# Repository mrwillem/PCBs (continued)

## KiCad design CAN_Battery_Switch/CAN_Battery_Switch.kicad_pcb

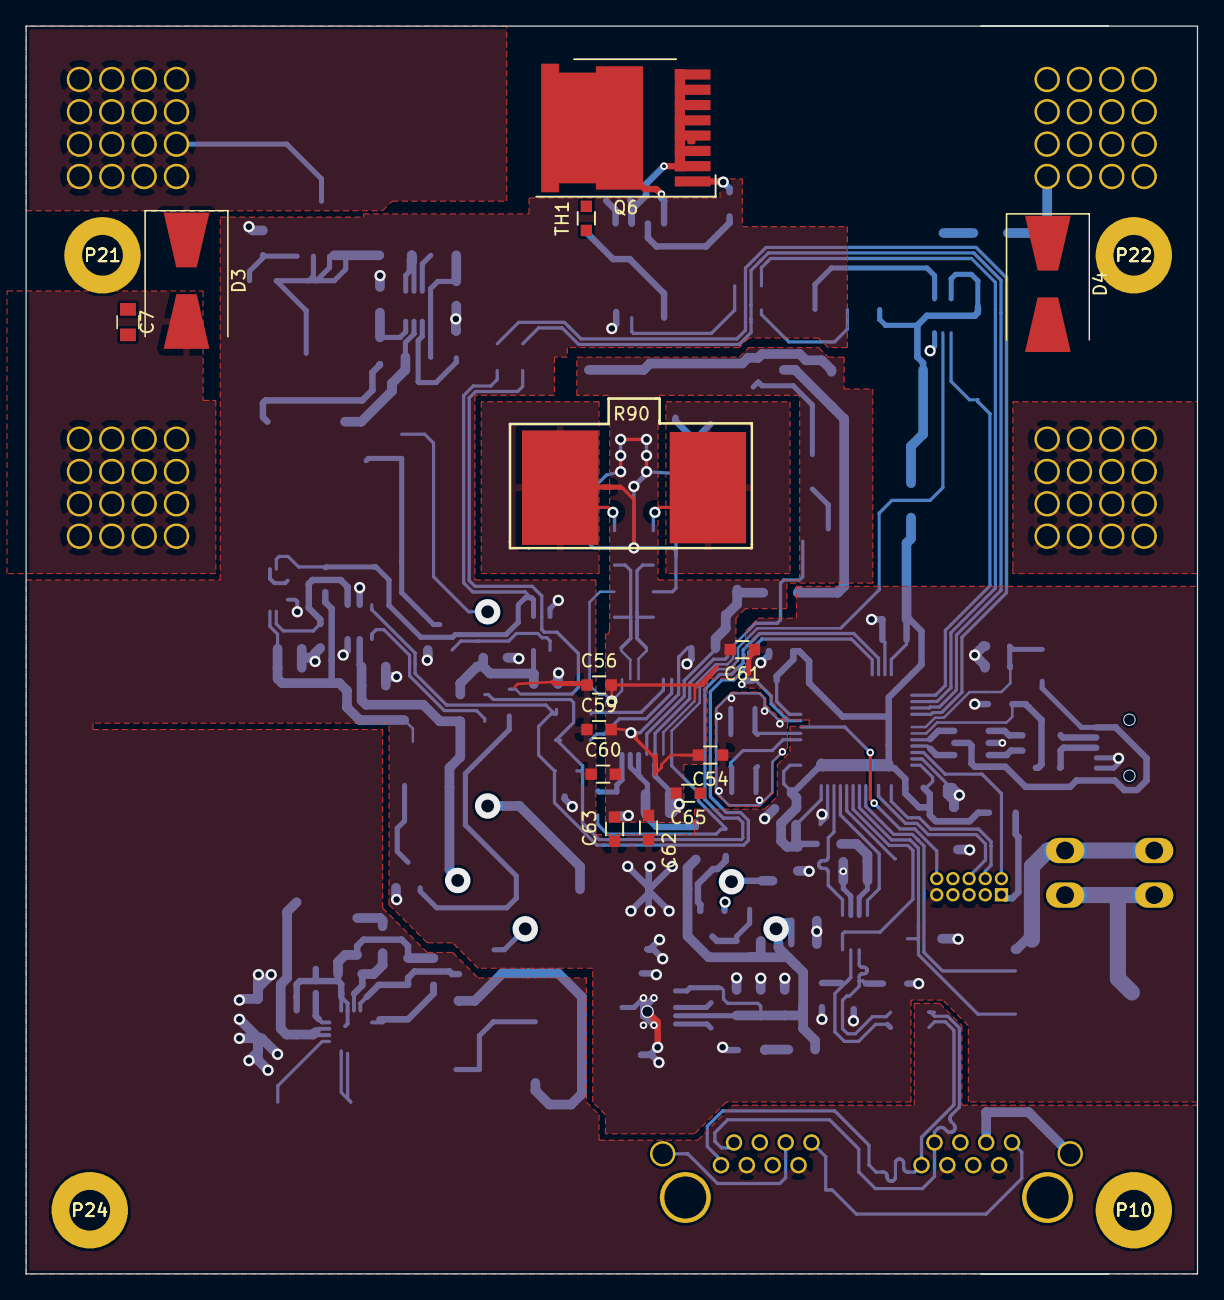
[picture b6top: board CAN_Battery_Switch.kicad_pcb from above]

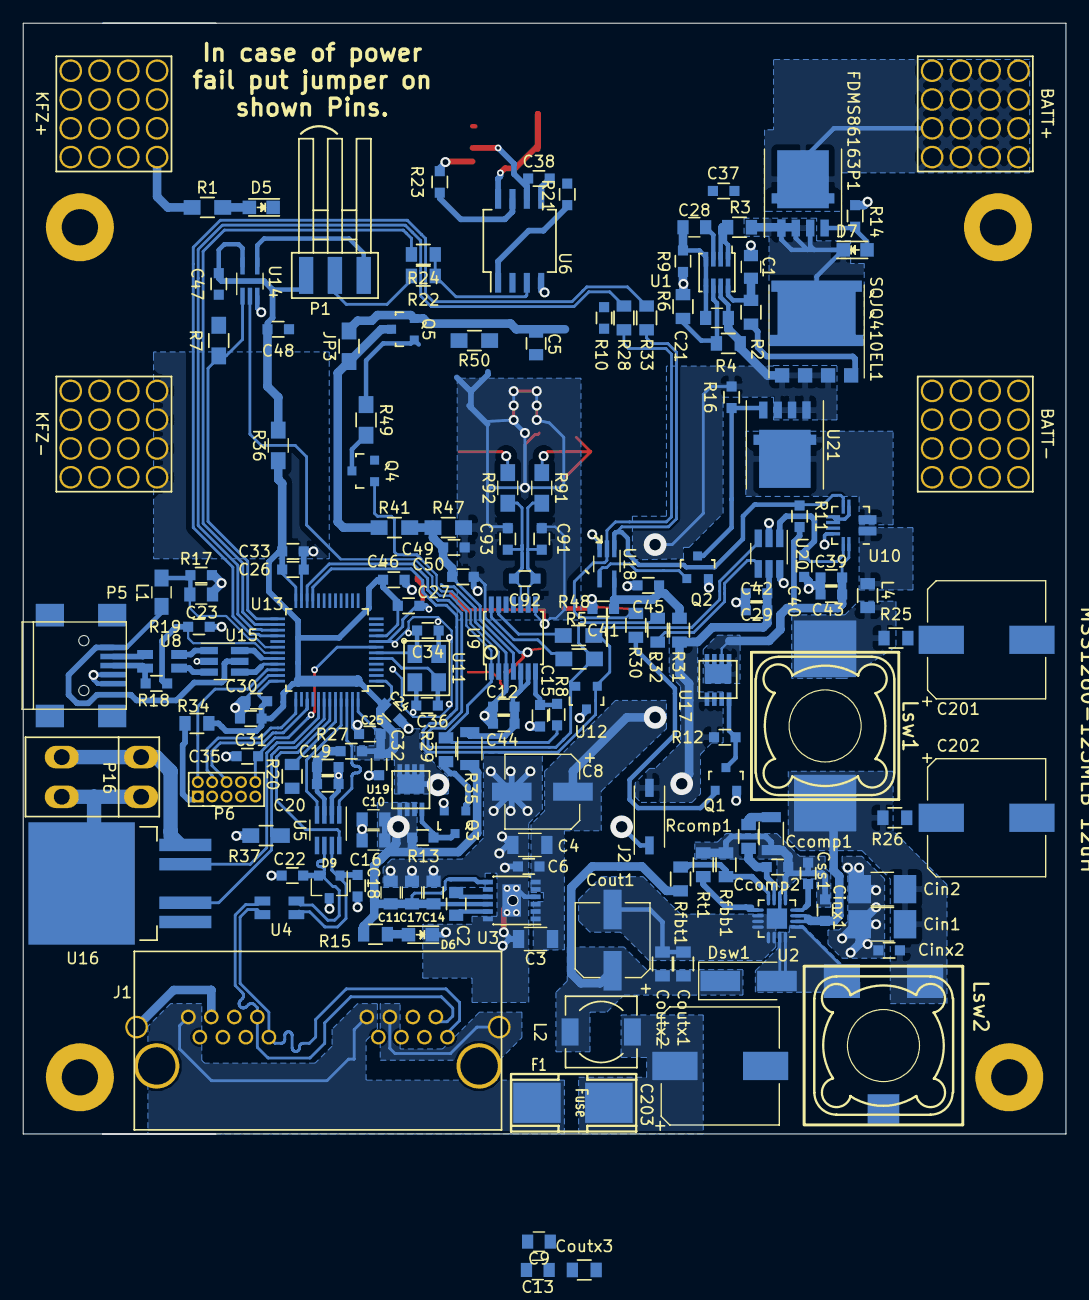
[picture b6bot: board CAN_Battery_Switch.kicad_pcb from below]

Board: 4 copper layers, 92.0 x 98.0 mm, 182 parts (163 on the bottom side), 105 nets.

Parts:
BATT+1: BATT+; WE_threaded_shank_M5_160A
BATT-1: BATT-; WE_threaded_shank_M5_160A
C1: 2nF; C_0805
C2: 1uF 0805ZC105KAT2A; C_0805
C3, C4: 4.7uF GRM31CR71H47; C_1206
C5, C10, C23: 100nF; C_0805
C6, C12, C18, C20, C22, C24, C25, C26, C27, C29, C30, C35, C37, C39, C41, C47, C49, C54, C56, C59, C60, C61, C62, C63, C65, C91, C92, C93: 100nF; R_0603_HandSolder
C7: 100pF 60V; C_0805
C8: 33uF; CP_Elec_6.3x7.7
C9: 10nF; C_0805
C11: 1nF; C_0805
C13, C17: 1uF GRM219R71E105KA88D; C_0805
C14, C16: 10uF; C_0805
C15: 1uF; R_0603_HandSolder
C19: 1uF GRM219R71E105KA88D; R_0603_HandSolder
C21: 470nF; C_0805
C28: 1uF; C_0805
C31, C32, C33, C45, C46, C48: 4,7uF; R_0603_HandSolder
C34, C36: 22pF; R_0603_HandSolder
C38: 120nF; R_0603_HandSolder
C40: 1 nF; R_0603_HandSolder
C42, C43: 10 uF; R_0603_HandSolder
C44: 10uF; R_0603_HandSolder
C50: 3,3nF; R_0603_HandSolder
C201, C202: CP; CP_Elec_10x10.5
C203: 100uF; CP_Elec_10x10.5
Ccomp1: 680nF; R_1206
Ccomp2: 12nF; R_0603_HandSolder
Cin1, Cin2: 4,7uF; C_1210_HandSoldering
Cinx1, Cinx2: 100nF; R_0603_HandSolder
Cout1: 10uF; CP_Elec_6.3x5.8
Coutx1, Coutx2, Coutx3: 1 uF; R_0805_HandSolder
Css1: 22nF; R_0603_HandSolder
D3, D4: P6KE16CA; D_SMB-SMC_Universal_Handsoldering
D5: BLUE; LED_0805
D6: RED; LED_0805
D7: BZG03C15TR; LED_0805
D9: D_Schottky_x2_ACom_KKA; SOT-23
Dsw1: SL44-E3/57T; D_SMA_Handsoldering
F1: Fuse; FSUPCMS
FDMS86163P1: FDMS86163P; DFN_5x6_SO8FL_Handsolder
J1: RJHSE-5380-02; RJHSE538X-02-noled
J2: CHS-01TA; SW_DIP_x1_W5.08mm_Slide_Copal_CHS-A
JP2: Jumper_NC_Small; NetTie0.4mmSMD
JP3: Jumper_NO_Small; R_0805_HandSoldering
KFZ+1: KFZ+; WE_threaded_shank_M5_160A
KFZ-1: KFZ-; WE_threaded_shank_M5_160A
L1: INDUCTOR; C_0805_HandSoldering
L2: 100nH; Choke_SMD_6.3x6.3_H3
L4: Ferrite_Bead; R_0805_HandSolder
Lsw1: MSS1260-123MLB 12uH; inductor_bourns_16uH
Lsw2: MSS1260-123MLB 12uH; inductor_Coilcraft_SER1390
P1: CONN_01X03; SMD_PIN_HEADER_01x03_angled
P5: USB_B; USB_Mini-B
P6: CONN_5X2; Pin_Header_Straight_2x05_Pitch1.27mm
P10: P10; hole
P16: CONN_01X02; weidmueller_2
P21: P21; hole
P22: P22; hole
P24: P24; hole
Q1, Q2, Q3, Q4: 2N7002; SOT-23
Q5: BSS84; SOT-23
Q6: Q_NMOS_GSD; Infineon_PG-HSOF-8-1
R1: 680R; R_0805_HandSoldering
R2: 10R; R_0805_HandSolder
R3: 29K; R_0805_HandSolder
R4, R22: 12K; R_0805_HandSolder
R5, R48, R91, R92: 100R; R_0805_HandSoldering
R6: 365K; R_0805_HandSolder
R7, R37: 10K; R_0805_HandSoldering
R8, R10, R11, R12, R13, R16: 10K; R_0603_HandSolder
R9: 2K2; R_0603_HandSolder
R14: 100K; R_0603_HandSolder
R15: R; R_0805_HandSolder
R17, R19: 47K; R_0603_HandSolder
R18: 1K5; R_0603_HandSolder
R20: 10K; R_0805_HandSolder
R21: 120R; R_0603_HandSolder
R23: R; R_0603_HandSolder
R24: 7K; R_0805_HandSolder
R25, R26: 0.0002R; R_0805_HandSolder
R27: 0R0; R_0603_HandSolder
R28, R33: 0R; R_0805_HandSolder
R29, R30, R31, R32, R34: 0R0; R_0805_HandSolder
R35: 0R0; R_1206
R36: 0R0; R_0805_HandSoldering
R41: 300K; R_0805_HandSoldering
R47: 16K5; R_0805_HandSoldering
R49: 169K; R_0805_HandSoldering
R50: 100K; R_0805_HandSoldering
R90: 0.0002R; WSLP_5931_DALE
Rcomp1: 634R; R_0805_HandSolder
Rfbb1: 10k; R_0805_HandSolder
Rfbt1: 232k; R_0805_HandSolder
Rt1: 78.9k; R_0805_HandSolder
SQJQ410EL1: SQJQ410EL; PowerPAK_8x8L
TH1: Thermistor_PTC; R_0603_HandSolder
U1: LTC4366-2; SOT23-8
U2: TPS55340-Q1; QFN-16-1EP_3x3mm_Pitch0.5mm_Hand_Soldering
U3: LTC3245; MSOP-12-1EP_3x4mm_Pitch0.65mm
U4, U8: USB-CMC-Wuerth; CMC-SMD-Wuerth
U5: TCAN330; SOT-23-8_Handsoldering
U6: AUIR3200S; SO-8_5.3x6.2mm_Pitch1.27mm
U9: BQ34Z100-G1; TSSOP-14_4.4x5mm_Pitch0.65mm
U10: ACS711EX; QFN-10-Allegro_ACS711EX
U11: 8MHz; Crystal_SMD_EuroQuartz_MT-4pin_3.2x2.5mm_hand
U12: AZ23c5v6; SOT-23
U13: STM32L433CC; LQFP-48_7x7mm_Pitch0.5mm
U14, U18: SN74LVC1G08; SOT-353_SC-70-5_Handsoldering
U15: USBLC6-2; SOT-23-6_Handsoldering
U16: BTS410; TO-263-4Lead
U17, U19: DMP4013LFG-7; Powerdi3333-8_Pitch0.65mm_Handsoldering
U20: MCP3421A0T-E/CH; SOT-23-6_Handsoldering
U21: NVMFS5A140PLZWFT1G; DFN_5x6_SO8FL_Handsolder

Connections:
3V3_3: C47.2, C48.2, P1.1, R36.2, U14.5
3VOUT: C9.1, C10.1, C11.1, C13.1, C14.2, C16.2, C17.1, J2.1, R13.1, R15.2, R35.1, U3.7, U3.10, U19.1, U19.2, U19.3
24VPREDIODE: D7.1, FDMS86163P1.1, FDMS86163P1.2, FDMS86163P1.3, R3.2, SQJQ410EL1.5
24VVIN: C3.1, C4.1, C5.1, C6.1, C8.1, C21.1, JP3.1, Q5.2, R4.2, R16.2, R50.2, SQJQ410EL1.1, SQJQ410EL1.2, SQJQ410EL1.3, U1.7, U3.1, U3.2, U3.3, U3.5, U3.6, U21.1, U21.2, U21.3
30V: Cout1.1, Coutx1.1, Coutx2.1, Dsw1.1, L2.2, Rfbt1.2
+2V5: C15.1, R8.1, U9.7
+3V3: C24.1, C25.1, C26.1, C27.1, C29.1, C30.1, C31.1, C32.1, C33.1, C42.2, C46.1, J2.2, R12.2, R27.2, R31.2, R34.2, R36.1, U13.1, U13.9, U13.24, U13.36, U13.48, U17.1, U17.2, U17.3, U19.5, U19.6, U19.7, U19.8, U20.5
ALARM: R8.2, R29.1, U9.1, U14.2
BATSENSE: C49.1, C50.1, R41.2, R47.1, U9.4
BATT+: BATT+1.1, C7.1, C37.2, D3.1, FDMS86163P1.5, Q6.3, R21.1, TH1.2, U6.8
BATT-: BATT-1.1, D3.2, JP2.2, R90.1, R91.1
BTS_CTRL_SIGNAL: P1.2, R22.2, U5.5
BTS_DIAG_SIGNAL: R24.2, U13.26
BTS_MCU_SIGNAL: R7.2, U13.25, U14.1
BTS_STATUS: U13.41, U16.4
BTS_SWITCH: R37.1, U13.42, U16.2
CALVINSHIELD: C5.2, C12.2, C15.2, C44.2, C49.2, C50.2, C54.2, C56.2, C59.2, C60.2, C61.2, C62.2, C63.2, C65.2, C91.1, C93.2, JP2.1, Q4.2, R47.2, U9.3, U9.8
CANRX: U5.4, U13.45
CANSHLD: J1.6, J1.14, J1.17
CANSLEEP: U5.8, U13.43
CANTX: U5.1, U13.46
DISCONNECT: R18.1, R19.2, U13.31
ECANH: J1.1, J1.9, U4.1
ECANL: J1.2, J1.10, U4.4
ECANV+: F1.1, J1.8, J1.16
EXTRESET: C35.1, P6.10, U13.7
GND: C39.2, C43.1, D5.1, Q3.2, U16.1
KFZ-: C1.2, C3.2, C4.2, C6.2, C7.2, C8.2, C9.2, C10.2, C11.2, C13.2, C14.1, C16.1, C17.2, C18.2, C19.1, C20.1, C22.2, C23.1, C24.2, C25.2, C26.2, C27.2, C29.2, C30.2, C31.2, C32.2, C33.2, C34.1, C35.2, C36.1, C37.1, C40.2, C41.2, C42.1, C45.2, C46.2, C47.1, C48.1, C54.1, C56.1, C59.1, C60.1, C61.1, C62.1, C63.1, C65.1, C201.2, C202.2, C203.2, Ccomp1.2, Ccomp2.2, Cin1.2, Cin2.2, Cinx1.2, Cinx2.2, Cout1.2, Coutx1.2, Coutx2.2, Coutx3.2, Css1.2, D4.2, D6.1, D9.3, J1.3, J1.7, J1.11, J1.15, KFZ-1.1, P5.4, P5.5, P6.3, P6.5, P6.7, P6.9, Q1.2, Q2.2, R6.1, R7.1, R9.1, R10.1, R14.1, R17.1, R19.1, R20.1, R37.2, R90.2, R92.2, Rfbb1.2, Rt1.2, U2.5, U2.6, U2.10, U2.11, U2.12, U2.13, U2.14, U2.17, U3.4, U3.12, U3.13, U5.2, U6.4, U10.3, U10.5, U10.6, U10.7, U10.8, U11.2, U11.4, U12.3, U13.8, U13.23, U13.35, U13.47, U14.3, U15.2, U18.3, U20.2, U20.6
KFZOUT: C38.1, D4.1, KFZ+1.1, Q6.2, R1.1, U6.6
unnamed: C1.1, R2.1, U1.8
unnamed: C2.1, U3.9
unnamed: C2.2, U3.11
unnamed: C12.1, C44.1, R35.2, U9.5, U9.6
unnamed: C18.1, D9.1, U4.2, U5.7
unnamed: C19.2, C20.2, R27.1, U5.3
unnamed: C21.2, C28.1, R9.2, U1.4, U1.5
unnamed: C22.1, D9.2, U4.3, U5.6
unnamed: C28.2, U1.3
unnamed: C34.2, U11.1, U13.6
unnamed: C36.2, U11.3, U13.5
unnamed: C38.2, U6.5
unnamed: C40.1, U10.9, U20.1
unnamed: C41.1, C45.1, R31.1, U18.5
unnamed: C91.2, C92.1, R91.2, U9.9
unnamed: C92.2, C93.1, R92.1, U9.10
unnamed: C201.1, R25.2
unnamed: C202.1, R26.2
unnamed: Ccomp1.1, Rcomp1.1
unnamed: Ccomp2.1, Rcomp1.2, U2.7
unnamed: Css1.1, U2.4
unnamed: D5.2, R1.2
unnamed: D6.2, R15.1
unnamed: D7.2, FDMS86163P1.4, R14.2
unnamed: JP3.2, Q5.3, R41.1
unnamed: P1.3, U14.4
unnamed: P5.2, U8.4
unnamed: P5.3, R18.2, U8.1
unnamed: P6.1, R34.1
unnamed: P16.1, U16.5
unnamed: P16.2, U16.3
unnamed: Q1.1, R30.2
unnamed: Q1.3, R12.1, U17.4
unnamed: Q2.1, U18.4
unnamed: Q2.3, R16.1, U21.4
unnamed: Q3.1, R29.2
unnamed: Q3.3, R13.2, U19.4
unnamed: Q4.3, R49.1
unnamed: Q5.1, R49.2, R50.1
unnamed: R2.2, SQJQ410EL1.4
unnamed: R3.1, U1.1, U1.2
unnamed: R4.1, R6.2, U1.6
unnamed: R5.2, U9.14
unnamed: R20.2, U13.44
unnamed: R21.2, U6.1
unnamed: R22.1, R24.1, U6.3
unnamed: R23.2, U6.7
unnamed: R28.2, U13.27
unnamed: R32.2, U20.4
unnamed: R33.2, U13.28
unnamed: R48.2, U9.13
unnamed: Rfbb1.1, Rfbt1.1, U2.8
unnamed: Rt1.1, U2.9
unnamed: TH1.1, U6.2
OV_CURRENT: R11.1, R33.1, U10.4, U18.1
PI-IN: L4.1, Lsw1.2, R25.1
PI-OUT: Cin1.1, Cin2.1, Cinx1.1, Cinx2.1, Lsw1.1, Lsw2.2, R26.1, U2.2, U2.3
POWERGATE: Q6.1, R23.1
PREFUSE: C203.1, Coutx3.1, F1.2, L2.1
SCL2: R48.1, U12.1, U13.21, U20.3
SDA2: R5.1, R32.1, U12.2, U13.22
SENSE_ENABLE: Q4.1, U9.2
SMPS_EN: R10.2, R28.1, R30.1, U13.2, U13.12, U18.2
SWCLK: P6.4, U13.37
SWDIO: P6.2, U13.34
SWO: P6.6, U13.39
SW_NODE: Dsw1.2, Lsw2.1, U2.1, U2.15, U2.16
TO_CURRENT_SENSOR: U10.2, U21.5
TO_SMPS: L4.2, U10.1
USBCONNECTED: C23.2, L1.1, R17.2, U13.30
USBD+: U8.2, U15.3
USBD+OUT: U13.33, U15.4
USBD-: U8.3, U15.1
USBD-OUT: U13.32, U15.6
USBVCC: L1.2, P5.1, U15.5
VSMPS: C39.1, C43.2, R11.2, U10.10, U17.5, U17.6, U17.7, U17.8
